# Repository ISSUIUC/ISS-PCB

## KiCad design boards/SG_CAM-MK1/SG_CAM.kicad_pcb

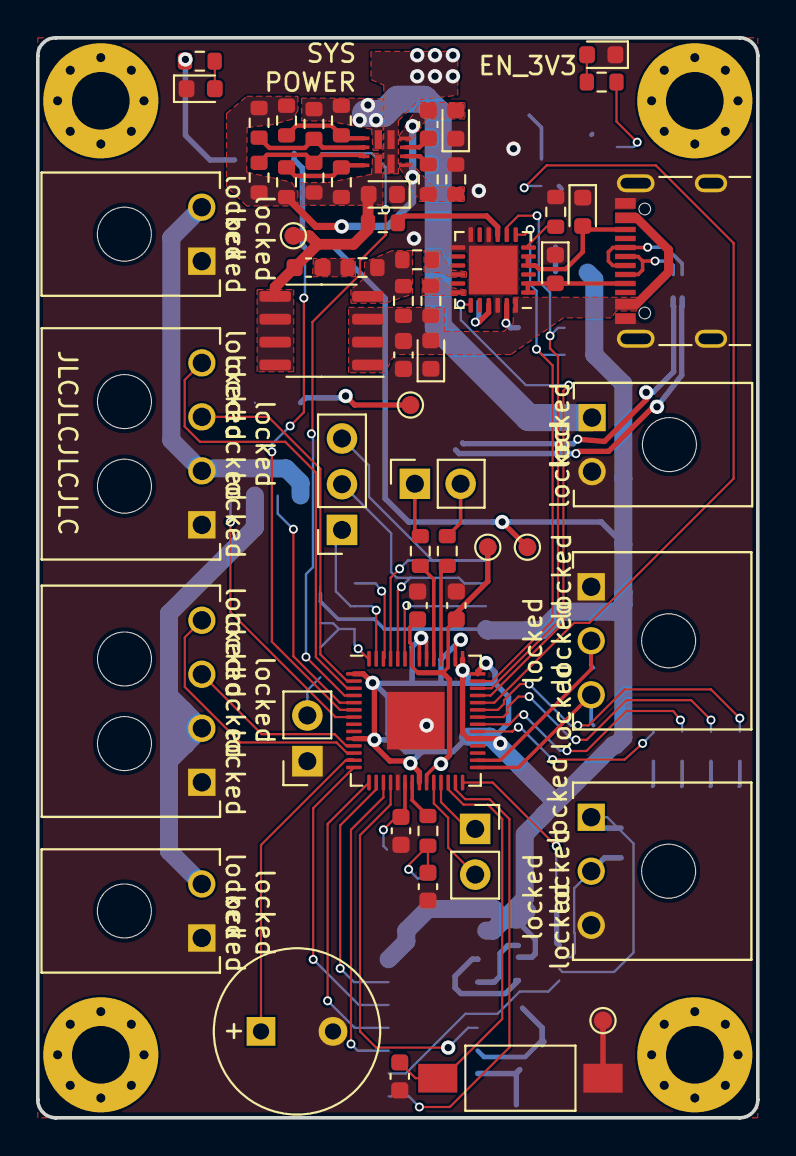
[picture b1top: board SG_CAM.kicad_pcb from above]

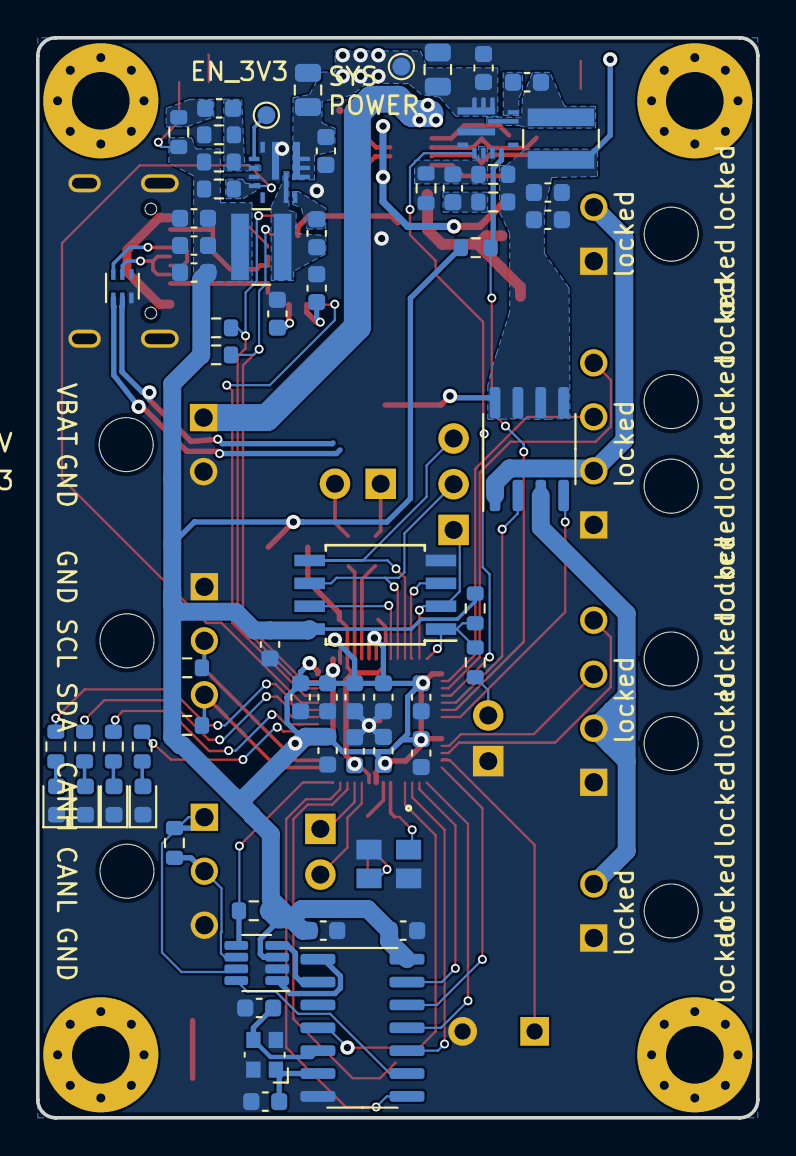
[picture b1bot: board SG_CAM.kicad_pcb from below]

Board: 2 copper layers, 40.0 x 60.0 mm, 129 parts (66 on the bottom side), 94 nets.

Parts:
BZ101: Buzzer; MagneticBuzzer_PUI_AT-0927-TT-6-R
C101, C102: 22pF; C_0603_1608Metric
C103, C105, C113, C129: 0.1uF; C_0603_1608Metric
C104, C106, C107, C108, C128, C132: 1uF; C_0603_1608Metric
C109, C110: 15uF; C_0805_2012Metric
C111, C112, C114, C115, C120, C126, C127, C130, C131, C133, C134, C135, C136, C137: 100nF; C_0603_1608Metric
C116, C117: 100pF; C_0603_1608Metric
C118, C119: 15pF; C_0603_1608Metric
C121, C123, C125: 10uF; C_0603_1608Metric
C122, C124: 22uF; C_0603_1608Metric
D101, D102, D103, D104, D105: D; D_0603_1608Metric
D106, D109: ORANGE LED; LED_0603_1608Metric
D107, D108: RED LED; LED_0603_1608Metric
D110: GREEN LED; LED_0603_1608Metric
D111: BLUE LED; LED_0603_1608Metric
H101, H102, H103, H104: MountingHole; MountingHole_3.2mm_M3_Pad_Via
J101: USB4105-GF-A; USB_C_Receptacle_GCT_USB4105-xx-A_16P_TopMnt_Horizontal
J102, J112, J115: Conn_01x02; PinSocket_1x02_P2.54mm_Vertical
J104, J107, J110: 2157601002; Molex_Micro-Fit-Plus_2157601002_1x02_P3.0mm
J105: 2157601003; Molex_Micro-Fit-Plus_2157601003_1x03_P3.0mm
J106, J109: 2157601004; Molex_Micro-Fit-Plus_2157601004_1x04_P3.0mm
J113: Conn_01x03; PinSocket_1x03_P2.54mm_Vertical
J114: Conn_01x03; Molex_Micro-Fit-Plus_2157601003_1x03_P3.0mm
L101: 2.2uH; L_Wuerth_MAPI-4020
L102: 5.6uH; L_Wuerth_MAPI-4020
Q101: DMP3085LSS; SO-8_3.9x4.9mm_P1.27mm
Q102: DMNH6022SSDQ; SO-8_3.9x4.9mm_P1.27mm
R101: 30k; R_0603_1608Metric
R102, R106, R111, R127, R129, R130: 10k; R_0603_1608Metric
R103, R107, R112, R117, R119, R120: 100k; R_0603_1608Metric
R104, R108: 5.1k; R_0603_1608Metric
R105: 47k; R_0603_1608Metric
R109: 0; R_0603_1608Metric
R110, R116, R122, R131: 1k; R_0603_1608Metric
R113: 18.7k; R_0603_1608Metric
R114: 120; R_0603_1608Metric
R115: 22k; R_0603_1608Metric
R118: 100; R_0603_1608Metric
R121, R125, R140, R141: 2.2k; R_0603_1608Metric
R123, R124: 20k; R_0603_1608Metric
R126: 45.3k; R_0603_1608Metric
R128: 140k; R_0603_1608Metric
R132, R135, R136, R137, R138, R139: 470; R_0603_1608Metric
R133, R134: 27.4; R_0603_1608Metric
SW101: SW_PUSH_RESET; SW_SPST_FSMSM
TP101, TP102, TP103, TP104, TP105, TP106, TP107: TestPoint; TestPoint_Pad_D1.0mm
U101: ECMF02-2AMX6; ST_UQFN-6L_1.5x1.7mm_P0.5mm
U102: MCP2518FDT-xSL; SOIC-14_3.9x8.7mm_P1.27mm
U103: TPS2121; VQFN-HR-RUX0012A
U104: TCAN337G; SOT-23-8
U105: STUSB4500QTR; QFN-24-1EP_4x4mm_P0.5mm_EP2.7x2.7mm
U106, U107: TI_TPS56637
U108: W25Q128JVSIM; SOIC-8W_5.3x5.3mm_P1.27mm
U109: RP2040; QFN-56-1EP_7x7mm_P0.4mm_EP3.2x3.2mm
Y101: 40MHz; Crystal_SMD_Abracon_ABM10-4Pin_2.5x2.0mm
Y102: ABM8-272-T3; Abracon_ABM8-272-T3_ABR_12.000MHZ

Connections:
+1V1: C126.1, C127.1, C128.1, TP104.1, U109.23 (DVDD), U109.45 (VREG_VOUT), U109.50 (DVDD)
+3V3: C103.2, C105.2, C120.1, C121.2, C123.2, C125.2, C130.1, C131.1, C132.1, C133.1, C134.1, C135.1, C136.1, C137.1, L101.2, R111.1, R119.2, R120.2, R121.2, R123.2, R125.1, R126.2, R130.2, R135.1, R140.1, R141.1, TP105.1, U102.14 (VDD), U104.3 (VCC), U108.8 (VCC), U109.1 (IOVDD), U109.10 (IOVDD), U109.22 (IOVDD), U109.33 (IOVDD), U109.42 (IOVDD), U109.43 (ADC_AVDD), U109.44 (VREG_IN), U109.48 (USB_VDD), U109.49 (IOVDD)
+9V: C122.2, C124.2, L102.2, Q102.5 (D2), Q102.6 (D2), Q102.7 (D1), Q102.8 (D1), R124.2, R128.2, R132.1, TP106.1
/BUZZER: BZ101.1 (-), U109.13 (GPIO10)
/CAM_1_POW: J106.2, J107.2, Q102.1 (S1)
/CAM_2_POW: J109.2, J110.2, Q102.3 (S2)
/CAN_FAULT: R111.2, U104.5 (FAULT), U109.28 (GPIO17)
/CAN_NCS: U102.13 (NCS), U109.16 (GPIO13)
/CAN_NINT: U102.4 (~INT), U109.18 (GPIO15)
/CAN_NINT1: U102.8 (~INT1/GPIO1), U109.27 (GPIO16)
/EN_3V3: TP103.1, U106.1 (EN)
/EN_9V: U107.1 (EN), U109.4 (GPIO2)
/LED_BLUE: R139.1, U109.37 (GPIO25)
/LED_GREEN: R138.1, U109.36 (GPIO24)
/LED_ORANGE: R137.1, U109.35 (GPIO23)
/LED_RED: R136.1, U109.34 (GPIO22)
/ON_OFF_1: Q102.2 (G1), U109.5 (GPIO3)
/ON_OFF_2: Q102.4 (G2), U109.7 (GPIO5)
/PG_3V3: R119.1, U106.4 (PG), U109.38 (GPIO26_ADC0)
/PG_9V: R120.1, U107.4 (PG), U109.6 (GPIO4)
/QSPI_CLK: J113.2, U108.6 (CLK), U109.52 (QSPI_SCLK)
/QSPI_IO0: J113.3, U108.5 (DI(IO0)), U109.53 (QSPI_SD0)
/QSPI_IO1: J113.1, U108.2 (DO(IO1)), U109.55 (QSPI_SD1)
/RESET_SW: C129.1, SW101.1, U109.26 (RUN)
/RX_1: J106.4, U109.3 (GPIO1)
/RX_2: J109.4, U109.12 (GPIO9)
/SCL: J114.2, R125.2, U109.30 (GPIO19)
/SDA: J114.3, R121.1, U109.29 (GPIO18)
/SPI_MISO: U102.11 (SDI), U109.15 (GPIO12)
/SPI_MOSI: U102.12 (SDO), U109.14 (GPIO11)
/SPI_SCK: U102.10 (SCK), U109.17 (GPIO14)
/SWCLK: J115.2, U109.24 (SWCLK)
/SWD: J115.1, U109.25 (SWD)
/SYS_POWER: C109.1, C110.1, C111.1, C112.1, TP102.1, U103.1 (OUT), U103.8 (OUT), U106.8 (VIN), U107.8 (VIN)
/TX_1: J106.3, U109.2 (GPIO0)
/TX_2: J109.3, U109.11 (GPIO8)
/USB_ALERT: U105.19 (ALERT), U109.39 (GPIO27_ADC1)
/USB_D+: J102.1, R133.1, U101.1 (D+_in)
/USB_D-: J102.2, R134.1, U101.2 (D-_in)
/USB_POWER: C113.1, D105.2 (A2), Q101.5 (D), Q101.6 (D), Q101.7 (D), Q101.8 (D), R101.1, R103.1, R116.1, TP101.1, U103.7 (IN1)
/USB_SCL: R141.2, U105.7 (SCL), U109.41 (GPIO29_ADC3)
/USB_SDA: R140.2, U105.8 (SDA), U109.40 (GPIO28_ADC2)
/VBAT: J104.1, R105.1, R107.1, U103.2 (IN2)
GND: BZ101.2 (+), C101.1, C102.2, C103.1, C104.2, C105.1, C107.2, C108.2, C109.2, C110.2, C111.2, C112.2, C118.2, C119.2, C120.2, C121.1, C122.1, C123.1, C124.1, C125.1, C126.2, C127.2, C128.2, C129.2, C130.2, C131.2, C132.2, C133.2, C134.2, C135.2, C136.2, C137.2, D101.1 (A1), D102.1 (K), D103.1 (A1), D104.1 (A1), D105.1 (A1), D106.1 (K), D107.1 (K), D108.1 (K), D109.1 (K), D110.1 (K), D111.1 (K), J101.A1 (GND), J101.A12 (GND), J101.B1 (GND), J101.B12 (GND), J101.S1 (SHIELD), J104.2, J105.3, J106.1, J107.1, J109.1, J110.1, J112.1, J114.1, R109.2, R112.2, R127.1, R129.1, SW101.2, TP107.1, U101.3 (GND), U102.7 (VSS), U104.2 (GND), U105.10 (GND), U105.12 (ADDR0), U105.13 (ADDR1), U105.22 (VSYS), U105.25 (GND), U106.3 (AGND), U106.9 (PGND), U106.10 (MODE), U107.3 (AGND), U107.9 (PGND), U107.10 (MODE), U108.4 (GND), U109.19 (TESTEN), U109.57 (GND), Y101.2, Y101.4, Y102.2, Y102.4
unnamed: C113.2, R118.2
unnamed: C116.1, R123.1
unnamed: C117.1, R124.1
unnamed: C119.1, R131.1, Y102.3
unnamed: C104.1, D101.2 (A2), J101.A4 (VBUS), J101.A9 (VBUS), J101.B4 (VBUS), J101.B9 (VBUS), Q101.1 (S), Q101.2 (S), Q101.3 (S), R110.2, R117.2, U105.24 (VDD)
unnamed: C106.1, D102.2 (A), R102.2, R104.2, R106.2, R108.2, R109.1, R113.1, U103.9 (ST), U103.12 (GND)
unnamed: D103.2 (A2), J101.B5 (CC2), U105.4 (CC2), U105.5 (CC2DB)
unnamed: D104.2 (A2), J101.A5 (CC1), U105.1 (CC1DB), U105.2 (CC1)
unnamed: D106.2 (A), R132.2
unnamed: D107.2 (A), R135.2
unnamed: D108.2 (A), R136.2
unnamed: D109.2 (A), R137.2
unnamed: D110.2 (A), R138.2
unnamed: D111.2 (A), R139.2
unnamed: J105.1, R114.2, U104.7 (CANH)
unnamed: J105.2, R114.1, U104.6 (CANL)
unnamed: J112.2, R122.1
unnamed: Q101.4 (G), R115.2, R117.1, R118.1
unnamed: J101.A6 (D+), J101.B6 (D+), U101.6 (D+_out)
unnamed: J101.A7 (D-), J101.B7 (D-), U101.5 (D-_out)
unnamed: C102.1, U102.6 (OSC1), Y101.1
unnamed: C101.2, U102.5 (OSC2), Y101.3
unnamed: U102.2 (RXCAN), U104.4 (RXD)
unnamed: U102.1 (TXCAN), U104.1 (TXD)
unnamed: U102.9 (~INT0/GPIO0/XSTBY), U104.8 (S)
unnamed: R105.2, R106.1, U103.3 (CP2)
unnamed: R113.2, U103.10 (ILM)
unnamed: R103.2, R104.1, U103.5 (OV1)
unnamed: R107.2, R108.1, U103.4 (OV2)
unnamed: R101.2, R102.1, U103.6 (PR1)
unnamed: C106.2, U103.11 (SS)
unnamed: R116.2, U105.9 (DISCH)
unnamed: R112.1, U105.6 (RESET)
unnamed: R115.1, U105.16 (VBUS_EN_SNK)
unnamed: R110.1, U105.18 (VBUS_VS_DISCH)
unnamed: C108.1, U105.21 (VREG_1V2)
unnamed: C107.1, U105.23 (VREG_2V7)
unnamed: C114.1, U106.7 (BOOT)
unnamed: C116.2, R126.1, R127.2, U106.2 (FB)
unnamed: C114.2, L101.1, U106.6 (SW)
unnamed: C115.1, U107.7 (BOOT)
unnamed: C117.2, R128.1, R129.2, U107.2 (FB)
unnamed: C115.2, L102.1, U107.6 (SW)
unnamed: U108.3 (IO2), U109.54 (QSPI_SD2)
unnamed: U108.7 (IO3), U109.51 (QSPI_SD3)
unnamed: R122.2, R130.1, U108.1 (~CS), U109.56 (QSPI_SS)
unnamed: R134.2, U109.46 (USB_DM)
unnamed: R133.2, U109.47 (USB_DP)
unnamed: C118.1, U109.20 (XIN), Y102.1
unnamed: R131.2, U109.21 (XOUT)

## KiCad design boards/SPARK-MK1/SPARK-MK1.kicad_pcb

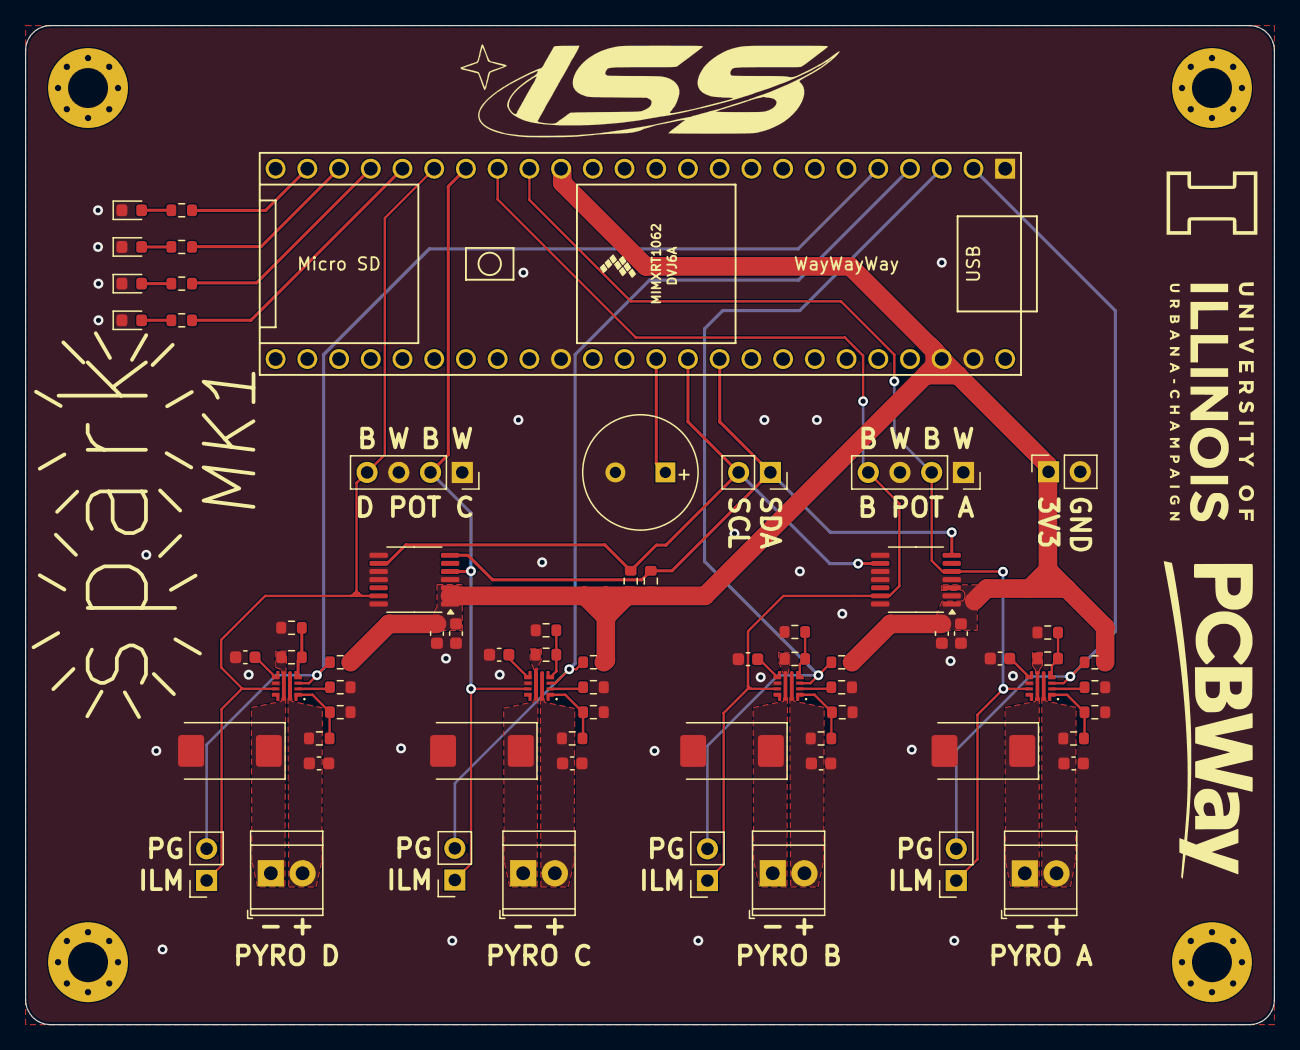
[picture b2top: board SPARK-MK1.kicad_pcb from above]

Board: 2 copper layers, 100.0 x 80.0 mm, 74 parts (0 on the bottom side), 45 nets.

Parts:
BZ101: Buzzer; MagneticBuzzer_PUI_AT-0927-TT-6-R
C101, C103, C105, C106, C107, C108: 1uF; C_0603_1608Metric
C102, C104: 100nF; C_0603_1608Metric
C109, C110, C111, C112: 5.1nF; C_0603_1608Metric
C113, C114, C115, C116: 470uF; CP_EIA-7343-43_Kemet-X
D101: RED LED; LED_0603_1608Metric
D102: ORANGE LED; LED_0603_1608Metric
D103: GREEN LED; LED_0603_1608Metric
D104: BLUE LED; LED_0603_1608Metric
H101, H102, H103, H104: M3; MountingHole_3.2mm_M3_Pad_Via
J101, J102: Conn_01x04; PinSocket_1x04_P2.54mm_Vertical
J103, J104, J105, J106: Screw_Terminal_01x02; TerminalBlock_TE_282834-2_1x02_P2.54mm_Horizontal
J107, J108, J109, J110, J111, J112: Conn_01x02; PinSocket_1x02_P2.54mm_Vertical
R101, R102: 4.12k; R_0603_1608Metric
R103, R104, R105, R106: 470; R_0603_1608Metric
R107, R108, R109, R110, R127, R128, R129, R130: 470k; R_0603_1608Metric
R111, R112, R113, R114: 105k; R_0603_1608Metric
R115, R116, R117, R118: 390k; R_0603_1608Metric
R119, R120, R121, R122: 47k; R_0603_1608Metric
R123, R124, R125, R126: 120k; R_0603_1608Metric
U101, U103: AD5252; TSSOP-14_4.4x5mm_P0.65mm
U102: Teensy4.1_bare; Teensy41_bare_pins
U104, U105, U106, U107: TPS25947; VQFN-HR-RPW0010A

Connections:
+3V3: C101.1, C102.1, C103.1, C104.1, J112.1, R101.2, R102.2, R119.2, R120.2, R121.2, R122.2, U101.1 (VDD), U101.3 (~WP), U102.15 (3V3), U102.46 (3V3), U103.1 (VDD), U103.2 (AD0), U103.3 (~WP)
/B1_A: J101.2, J108.1, U101.5 (B1), U102.16 (24_A10_TX6_SCL2), U104.9 (ILM)
/B1_B: J102.2, J110.1, U102.18 (26_A12_MOSI1), U103.5 (B1), U106.9 (ILM)
/B3_A: J101.4, J109.1, U101.13 (B3), U102.17 (25_A11_RX6_SDA2), U105.9 (ILM)
/B3_B: J102.4, J111.1, U102.19 (27_A13_SCK1), U103.13 (B3), U107.9 (ILM)
/BUZZER: BZ101.1 (-), U102.37 (15_A1_RX3_SPDIF_IN)
/DVDT_6V_A: C109.1, U104.7 (DVDT)
/DVDT_6V_B: C110.1, U105.7 (DVDT)
/DVDT_6V_C: C111.1, U106.7 (DVDT)
/DVDT_6V_D: C112.1, U107.7 (DVDT)
/I2C_SCL: J107.2, R102.1, U101.9 (SCL), U102.38 (16_A2_RX4_SCL1), U103.9 (SCL)
/I2C_SDA: J107.1, R101.1, U101.7 (SDA), U102.39 (17_A3_TX4_SDA1), U103.7 (SDA)
/LED_BLUE: R106.1, U102.23 (31_CTX3)
/LED_GREEN: R105.1, U102.22 (30_CRX3)
/LED_ORANGE: R104.1, U102.21 (29_TX7)
/LED_RED: R103.1, U102.20 (28_RX7)
/OVLO_6V_A: R115.1, U104.2 (OVLO/OVCSEL)
/OVLO_6V_B: R116.1, U105.2 (OVLO/OVCSEL)
/OVLO_6V_C: R117.1, U106.2 (OVLO/OVCSEL)
/OVLO_6V_D: R118.1, U107.2 (OVLO/OVCSEL)
/PGTH_6V_A: R123.1, R127.1, U104.4 (PGTH/NFLT)
/PGTH_6V_B: R124.1, R128.1, U105.4 (PGTH/NFLT)
/PGTH_6V_C: R125.1, R129.1, U106.4 (PGTH/NFLT)
/PGTH_6V_D: R126.1, R130.1, U107.4 (PGTH/NFLT)
/PG_EF_A: J108.2, R119.1, U102.2 (0_RX1_CRX2_CS1), U104.3 (PG/AUXOFF)
/PG_EF_B: J109.2, R120.1, U102.3 (1_TX1_CTX2_MISO1), U105.3 (PG/AUXOFF)
/PG_EF_C: J110.2, R121.1, U102.4 (2_OUT2), U106.3 (PG/AUXOFF)
/PG_EF_D: J111.2, R122.1, U102.5 (3_LRCLK2), U107.3 (PG/AUXOFF)
/PYRO_A: C105.1, J103.2, R107.1, U104.5 (IN)
/PYRO_A_OUT: C113.1, J103.1, R127.2, U104.6 (OUT)
/PYRO_B: C106.1, J104.2, R108.1, U105.5 (IN)
/PYRO_B_OUT: C114.1, J104.1, R128.2, U105.6 (OUT)
/PYRO_C: C107.1, J105.2, R109.1, U106.5 (IN)
/PYRO_C_OUT: C115.1, J105.1, R129.2, U106.6 (OUT)
/PYRO_D: C108.1, J106.2, R110.1, U107.5 (IN)
/PYRO_D_OUT: C116.1, J106.1, R130.2, U107.6 (OUT)
/UVLO_6V_A: R107.2, R111.1, U104.1 (EN/UVLO)
/UVLO_6V_B: R108.2, R112.1, U105.1 (EN/UVLO)
/UVLO_6V_C: R109.2, R113.1, U106.1 (EN/UVLO)
/UVLO_6V_D: R110.2, R114.1, U107.1 (EN/UVLO)
GND: BZ101.2 (+), C101.2, C102.2, C103.2, C104.2, C105.2, C106.2, C107.2, C108.2, C109.2, C110.2, C111.2, C112.2, C113.2, C114.2, C115.2, C116.2, D101.1 (K), D102.1 (K), D103.1 (K), D104.1 (K), J101.1, J101.3, J102.1, J102.3, J112.2, R111.2, R112.2, R113.2, R114.2, R115.2, R116.2, R117.2, R118.2, R123.2, R124.2, R125.2, R126.2, U101.2 (AD0), U101.4 (W1), U101.8 (VSS), U101.10 (DGND), U101.11 (AD1), U101.14 (W3), U102.1 (GND), U102.34 (GND), U102.47 (GND), U103.4 (W1), U103.8 (VSS), U103.10 (DGND), U103.11 (AD1), U103.14 (W3), U104.8 (GND), U105.8 (GND), U106.8 (GND), U107.8 (GND)
unnamed: D101.2 (A), R103.2
unnamed: D102.2 (A), R104.2
unnamed: D103.2 (A), R105.2
unnamed: D104.2 (A), R106.2

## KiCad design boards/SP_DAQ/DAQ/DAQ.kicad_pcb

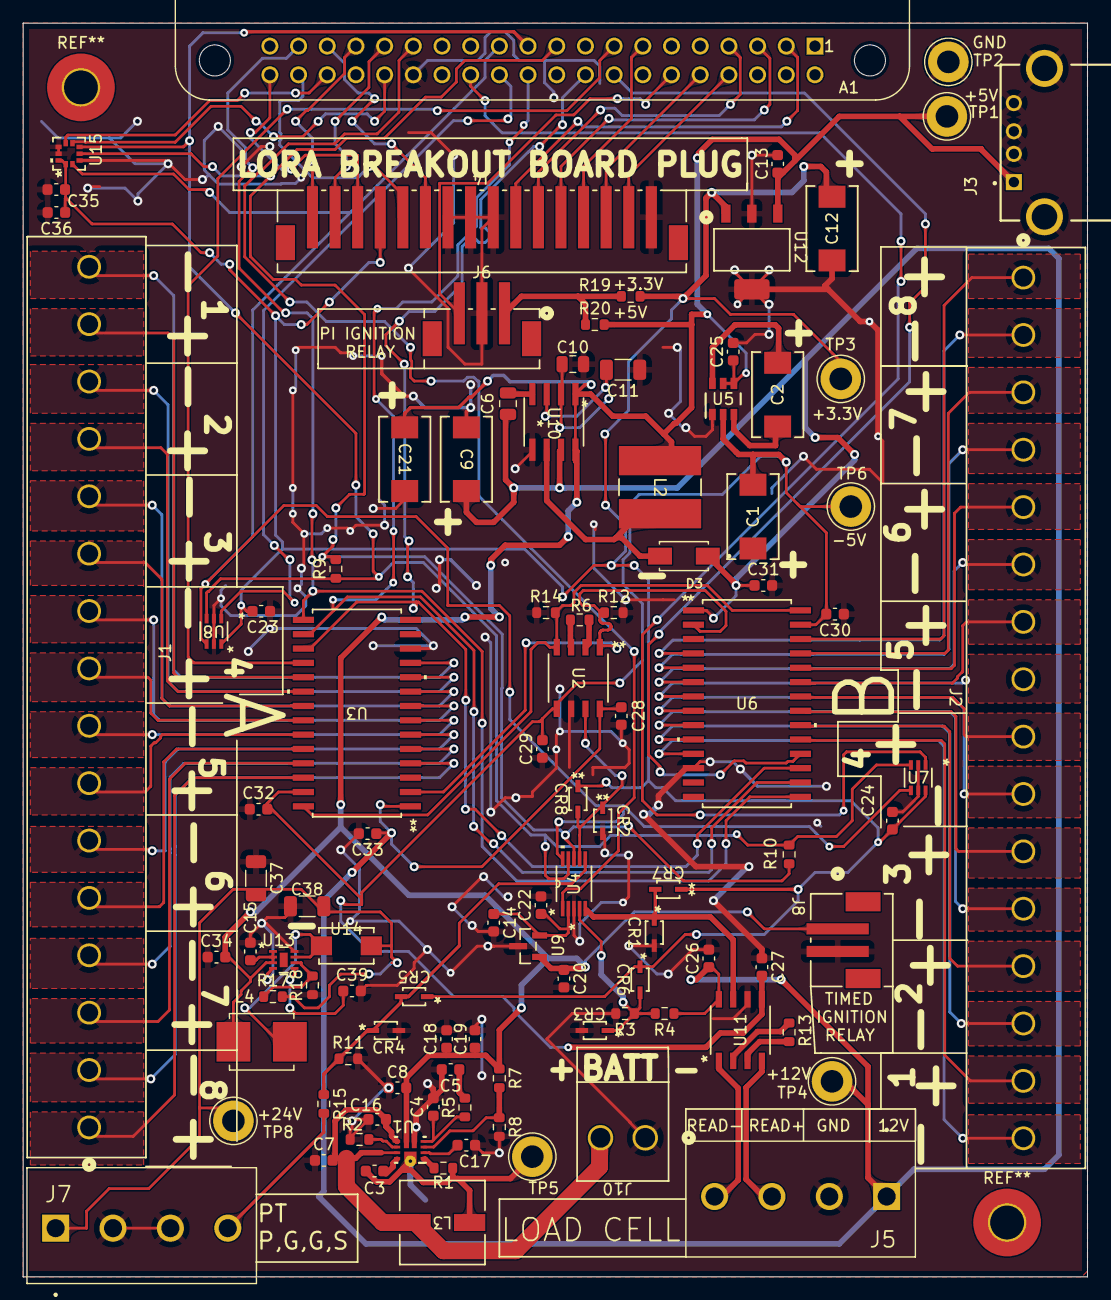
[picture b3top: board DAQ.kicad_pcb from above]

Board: 2 copper layers, 94.2 x 111.0 mm, 102 parts (0 on the bottom side), 96 nets.

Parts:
A1: ADA3708; ADA3708_RPI-ZERO
C1, C2, C9, C12, C21: 33uF; TPSD336M020R0200_AVX
C3, C15, C16, C22, C23, C24, C25, C26, C27, C28, C29, C30, C31, C32, C33, C39: 0.1uF; C_0603_1608Metric
C4, C5: 4.7nF; C_0603_1608Metric
C6: 0.001uF; C_0805_2012Metric
C7, C8, C18, C19: 22uF; C_0603_1608Metric
C10: 0.1uF; C_0805_2012Metric
C11: 0.047uF; C_1206_3216Metric
C13, C20: 0.47uF; C_0603_1608Metric
C14: 1uF; C_0603_1608Metric
C17: 2.2uF1; C_0603_1608Metric
C34: 2.2uF; C_0603_1608Metric
C35: 100nF; C_0603_1608Metric
C36: 4.7uF; C_0603_1608Metric
C37, C38: 4.7uF; C_1206_3216Metric
CR1, CR2, CR3, CR4, CR5, CR6, CR7, CR8: CUS08F30_H3F; USC_TOS
D3: SS12; DIOM4325X250N
J1, J2: Screw_Terminal_01x16; CONN16_TB007-508_CUD
J3: USB1130-15-A_REVA; GCT_USB1130-15-A_REVA
J4: B16B-PH-SM4-TBLFSN; CONN_B16B-PH-SM4-TB_JST
J5, J7: Load_Cell_terminal; CUI_TB007-508-04BE
J6: B3B-PH-SM4-TBLFSN; CONN_B3B-PH-SM4-TB_03P_JST
J8: B2B-PH-SM4-TBLFSN; CONN_B2B-PH-SM4-TBLFSN_JST
J10: B2P-VHLFSN; CONN_B2P-VH_JST
L2: 18uH; IND_BOURNS_SRR6038
L3: 744311220; IND_7040-WE-HCI_WRE
L4: LQH55DN100M03L; IND_LQH55DN100M03L
R1: 330k; R_0603_1608Metric
R2: 110k; R_0603_1608Metric
R3, R8: 100k; R_0603_1608Metric
R4: 300k; R_0603_1608Metric
R5: 17.4k; R_0603_1608Metric
R6: 630; R_0603_1608Metric
R7: 312k; R_0603_1608Metric
R9, R10: 10k; R_0603_1608Metric
R11: 976; R_0603_1608Metric
R12, R14: 47 k; R_0603_1608Metric
R13: 176; R_0603_1608Metric
R15: 2000; R_0603_1608Metric
R17: 9.1k; R_0603_1608Metric
R18: 499; R_0603_1608Metric
R19, R20: 0; R_0603_1608Metric
TP1, TP2, TP3, TP4, TP5, TP6, TP8: TestPoint; TestPoint_Loop_D3.80mm_Drill2.0mm
U1: TPS61089RNRR; RNR0011A
U2, U11: INA819ID; D8_TEX
U3, U6: MUX507IDWR; DW28_TEX
U4: ADC124S051CIMMX/NOPB; MUB10A
U5: LM2664M6X/NOPB; DBV0006A_N
U7, U8: TMP126NDCKR; SC70-6_DCK_TEX
U9: REF3133AIDBZR; DBZ3
U10: TPS6734IDR; D8
U12: LM3940IMP-3.3/NOPB; MP04A
U13: MIC2601YML-TR; MLF-8_ML_MCH
U14: B360A-13-F; B360A-13-F_DIO
U15: LPS25HBTR; HLGA10_2P5X2P5_STM

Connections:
+3.3V: C12.2, C23.1, C24.1, C35.1, C36.1, CR5.1, CR6.1, CR7.1, CR8.1, J4.13, R19.1, TP3.1, U7.6 (VDD), U8.6 (VDD), U12.3 (OUT), U15.1 (VDD_IO), U15.10 (VDD)
+5V: C8.1, C13.2, C15.2, C18.1, C19.1, C20.1, C21.1, C25.1, C34.2, J3.1 (VCC), J8.1, L2.1, L4.1, R7.1, R20.2, TP1.1, U1.6 (VOUT), U5.4 (SD_N), U5.5 (V+), U9.1 (IN), U10.1 (EN), U10.8 (VCC), U12.1 (IN), U13.1 (VIN), U13.2 (VDD), U13.3 (EN)
+12V: C6.2, C9.2, C26.1, C28.2, C31.1, C33.1, D3.C, J5.1, R4.1, TP4.1, U2.8 (+VS), U3.1 (VDD), U6.1 (VDD), U10.7 (FB), U11.8 (+VS)
+24V: C37.2, C38.2, J7.1, R17.2, TP8.1, U14.2
-5V: C1.2, C27.2, C29.2, C30.2, C32.2, TP6.1, U2.5 (-VS), U3.27 (VSS), U5.2 (OUT), U6.27 (VSS), U11.5 (-VS)
/12V_CALIBRATION: CR3.1, CR6.2, R3.1, R4.2, U4.4 (IN4)
/ADC_U4_CS_LINE: A1.29 (GPIO5), U4.1 (~CS)
/D+: J5.3, U11.4 (+IN)
/D-: J5.4, U11.1 (-IN)
/IGNITION_SWITCH: A1.12 (GPIO18), J6.3
/INA819ID-IN_LINE: R12.1, U2.1 (-IN), U3.2 (DB), U6.2 (DB)
/INA819ID_+IN_LINE: R14.2, U2.4 (+IN), U3.28 (DA), U6.28 (DA)
/LOAD_CELL_LINE: CR1.1, CR7.2, U4.5 (IN3), U11.7 (OUT)
/LORA_CS_NSS_LINE: A1.5 (GPIO3/SCL), J4.5
/LORA_DIO0: A1.13 (GPIO27/GEN2), J4.4
/LORA_DIO1: A1.31 (GPIO6), J4.15
/LORA_DIO2: A1.33 (GPIO13), J4.16
/LORA_DIO3: A1.8 (TXD0/GPIO14), J4.2
/LORA_DIO4: A1.10 (RXD0/GPIO15), J4.3
/LORA_DIO5: A1.3 (GPIO2/SDA), J4.7
/LORA_RESET: A1.7 (GPIO4/GPCKL0), J4.6
/MISO_LINE: A1.21 (GPIO9/MISO), R9.1, R10.1, U4.9 (DOUT), U7.3 (SIO), U8.3 (SIO), U15.5 (SDO/SA0)
/MISO_LINE2: A1.35 (GPIO19), J4.11
/MOSI_LINE: A1.19 (GPIO10/MOSI), R9.2, R10.2, U4.8 (DIN), U15.4 (SDA/SDI/SDO)
/MOSI_LINE2: A1.38 (GPIO20), J4.12
/MUX_A0: A1.18 (GEN5/GPIO24), U3.17 (A0), U6.17 (A0)
/MUX_A1: A1.22 (GEN/6GPIO25), U3.16 (A1), U6.16 (A1)
/MUX_A2: A1.37 (GPIO26), U3.15 (A2), U6.15 (A2)
/PRE-BOOST_LINE: C7.2, C16.2, J10.2, L3.2, U1.7 (EN), U1.9 (VIN)
/PRESSURE_TRANSMITTER_LINE: CR4.1, CR5.2, R11.1, R15.1, U4.6 (IN2)
/SCLK_LINE: A1.23 (GPIO11/SCLK), U4.10 (SCLK), U7.4 (SCLK), U8.4 (SCLK), U15.2 (SCL/SPC)
/SCLK_LINE2: A1.40 (GPIO21), J4.14
/TEMPERATURE_SENSOR_U7_CS_LINE: A1.26 (~CE1/~GPIO7), U7.1 (*CS)
/TEMPERATURE_SENSOR_U8_CS_LINE: A1.24 (~CE0/GPIO8), U8.1 (*CS)
/THERMO_AMP_LINE: CR2.1, CR8.2, U2.7 (OUT), U4.7 (IN1)
/U3_ENABLE: A1.15 (GPIO22/GEN3), U3.18 (EN)
/U6_ENABLE: A1.16 (GEN4/GPIO23), U6.18 (EN)
/U15_CS_LINE: A1.32 (GPIO12), U15.6 (CS)
/U15_INTERRUPT: A1.36 (GPIO16), U15.7 (INT_DRDY)
GND: A1.30 (GND[6]), C1.1, C4.2, C5.2, C7.1, C8.2, C9.1, C10.1, C11.1, C12.1, C13.1, C14.2, C15.1, C16.1, C17.1, C18.2, C19.2, C20.2, C21.2, C22.2, C23.2, C24.2, C25.2, C26.2, C27.1, C28.1, C29.1, C30.1, C31.2, C32.1, C33.2, C34.1, C35.2, C36.2, C37.1, C38.1, C39.2, CR1.2, CR2.2, CR3.2, CR4.2, J3.2 (D-), J3.3 (D+), J3.4 (GND), J3.S1 (SHIELD), J3.S2 (SHIELD__1), J4.1, J4.8, J4.9, J4.10, J5.2, J6.2, J7.2, J7.3, J8.2, J10.1, R2.2, R3.2, R8.2, R11.2, R12.2, R14.1, R18.1, TP2.1, U1.5 (GND), U2.6 (REF), U3.12 (GND), U4.3 (GND), U5.1 (GND), U6.12 (GND), U7.2 (GND), U7.5 (*ALERT), U8.2 (GND), U8.5 (*ALERT), U9.3 (GND), U10.5 (GND), U11.6 (REF), U12.2 (GND), U12.4 (GND), U13.4 (AGND), U13.8 (PGND), U15.3 (RES), U15.8 (GND), U15.9 (GND)
unnamed: C5.1, R5.2
unnamed: J1.1, U3.26 (S8A)
unnamed: J1.2, U3.4 (S8B)
unnamed: J1.3, U3.25 (S7A)
unnamed: J1.4, U3.5 (S7B)
unnamed: J1.5, U3.24 (S6A)
unnamed: J1.6, U3.6 (S6B)
unnamed: J1.7, U3.23 (S5A)
unnamed: J1.8, U3.7 (S5B)
unnamed: J1.9, U3.22 (S4A)
unnamed: J1.10, U3.8 (S4B)
unnamed: J1.11, U3.21 (S3A)
unnamed: J1.12, U3.9 (S3B)
unnamed: J1.13, U3.20 (S2A)
unnamed: J1.14, U3.10 (S2B)
unnamed: J1.15, U3.19 (S1A)
unnamed: J1.16, U3.11 (S1B)
unnamed: J2.1, U6.26 (S8A)
unnamed: J2.2, U6.4 (S8B)
unnamed: J2.3, U6.25 (S7A)
unnamed: J2.4, U6.5 (S7B)
unnamed: J2.5, U6.24 (S6A)
unnamed: J2.6, U6.6 (S6B)
unnamed: J2.7, U6.23 (S5A)
unnamed: J2.8, U6.7 (S5B)
unnamed: J2.9, U6.22 (S4A)
unnamed: J2.10, U6.8 (S4B)
unnamed: J2.11, U6.21 (S3A)
unnamed: J2.12, U6.9 (S3B)
unnamed: J2.13, U6.20 (S2A)
unnamed: J2.14, U6.10 (S2B)
unnamed: J2.15, U6.19 (S1A)
unnamed: J2.16, U6.11 (S1B)
unnamed: J6.1, R19.2, R20.1
unnamed: J7.4, R15.2
unnamed: R6.1, U2.2 (RG)
unnamed: R6.2, U2.3 (RG)
unnamed: R13.1, U11.2 (RG)
unnamed: R13.2, U11.3 (RG)
unnamed: C3.1, U1.10 (BOOT)
unnamed: C4.1, R5.1, U1.4 (COMP)
unnamed: R7.2, R8.1, U1.3 (FB)
unnamed: R1.1, U1.1 (FSW)
unnamed: R2.1, U1.8 (ILIM)
unnamed: C3.2, L3.1, R1.2, TP5.1, U1.11 (SW), U1.V
unnamed: C17.2, U1.2 (VCC)
unnamed: C14.1, C22.1, U4.2 (VA), U9.2 (OUT)
unnamed: C2.2, U5.6 (CAP+)
unnamed: C2.1, U5.3 (CAP-)
unnamed: C6.1, U10.4 (COMP)
unnamed: D3.A, L2.2, U10.6 (OUT)
unnamed: C10.2, U10.2 (REF)
unnamed: C11.2, U10.3 (SS)
unnamed: R17.1, R18.2, U13.6 (FB)
unnamed: C39.1, U13.5 (SS)
unnamed: L4.2, U13.7 (SW), U14.1
